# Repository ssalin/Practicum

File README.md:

# Practicum

adding the following libraries for eagle:

https://github.com/sparkfun/SparkFun-Eagle-Libraries
https://github.com/adafruit/Adafruit-Eagle-Library

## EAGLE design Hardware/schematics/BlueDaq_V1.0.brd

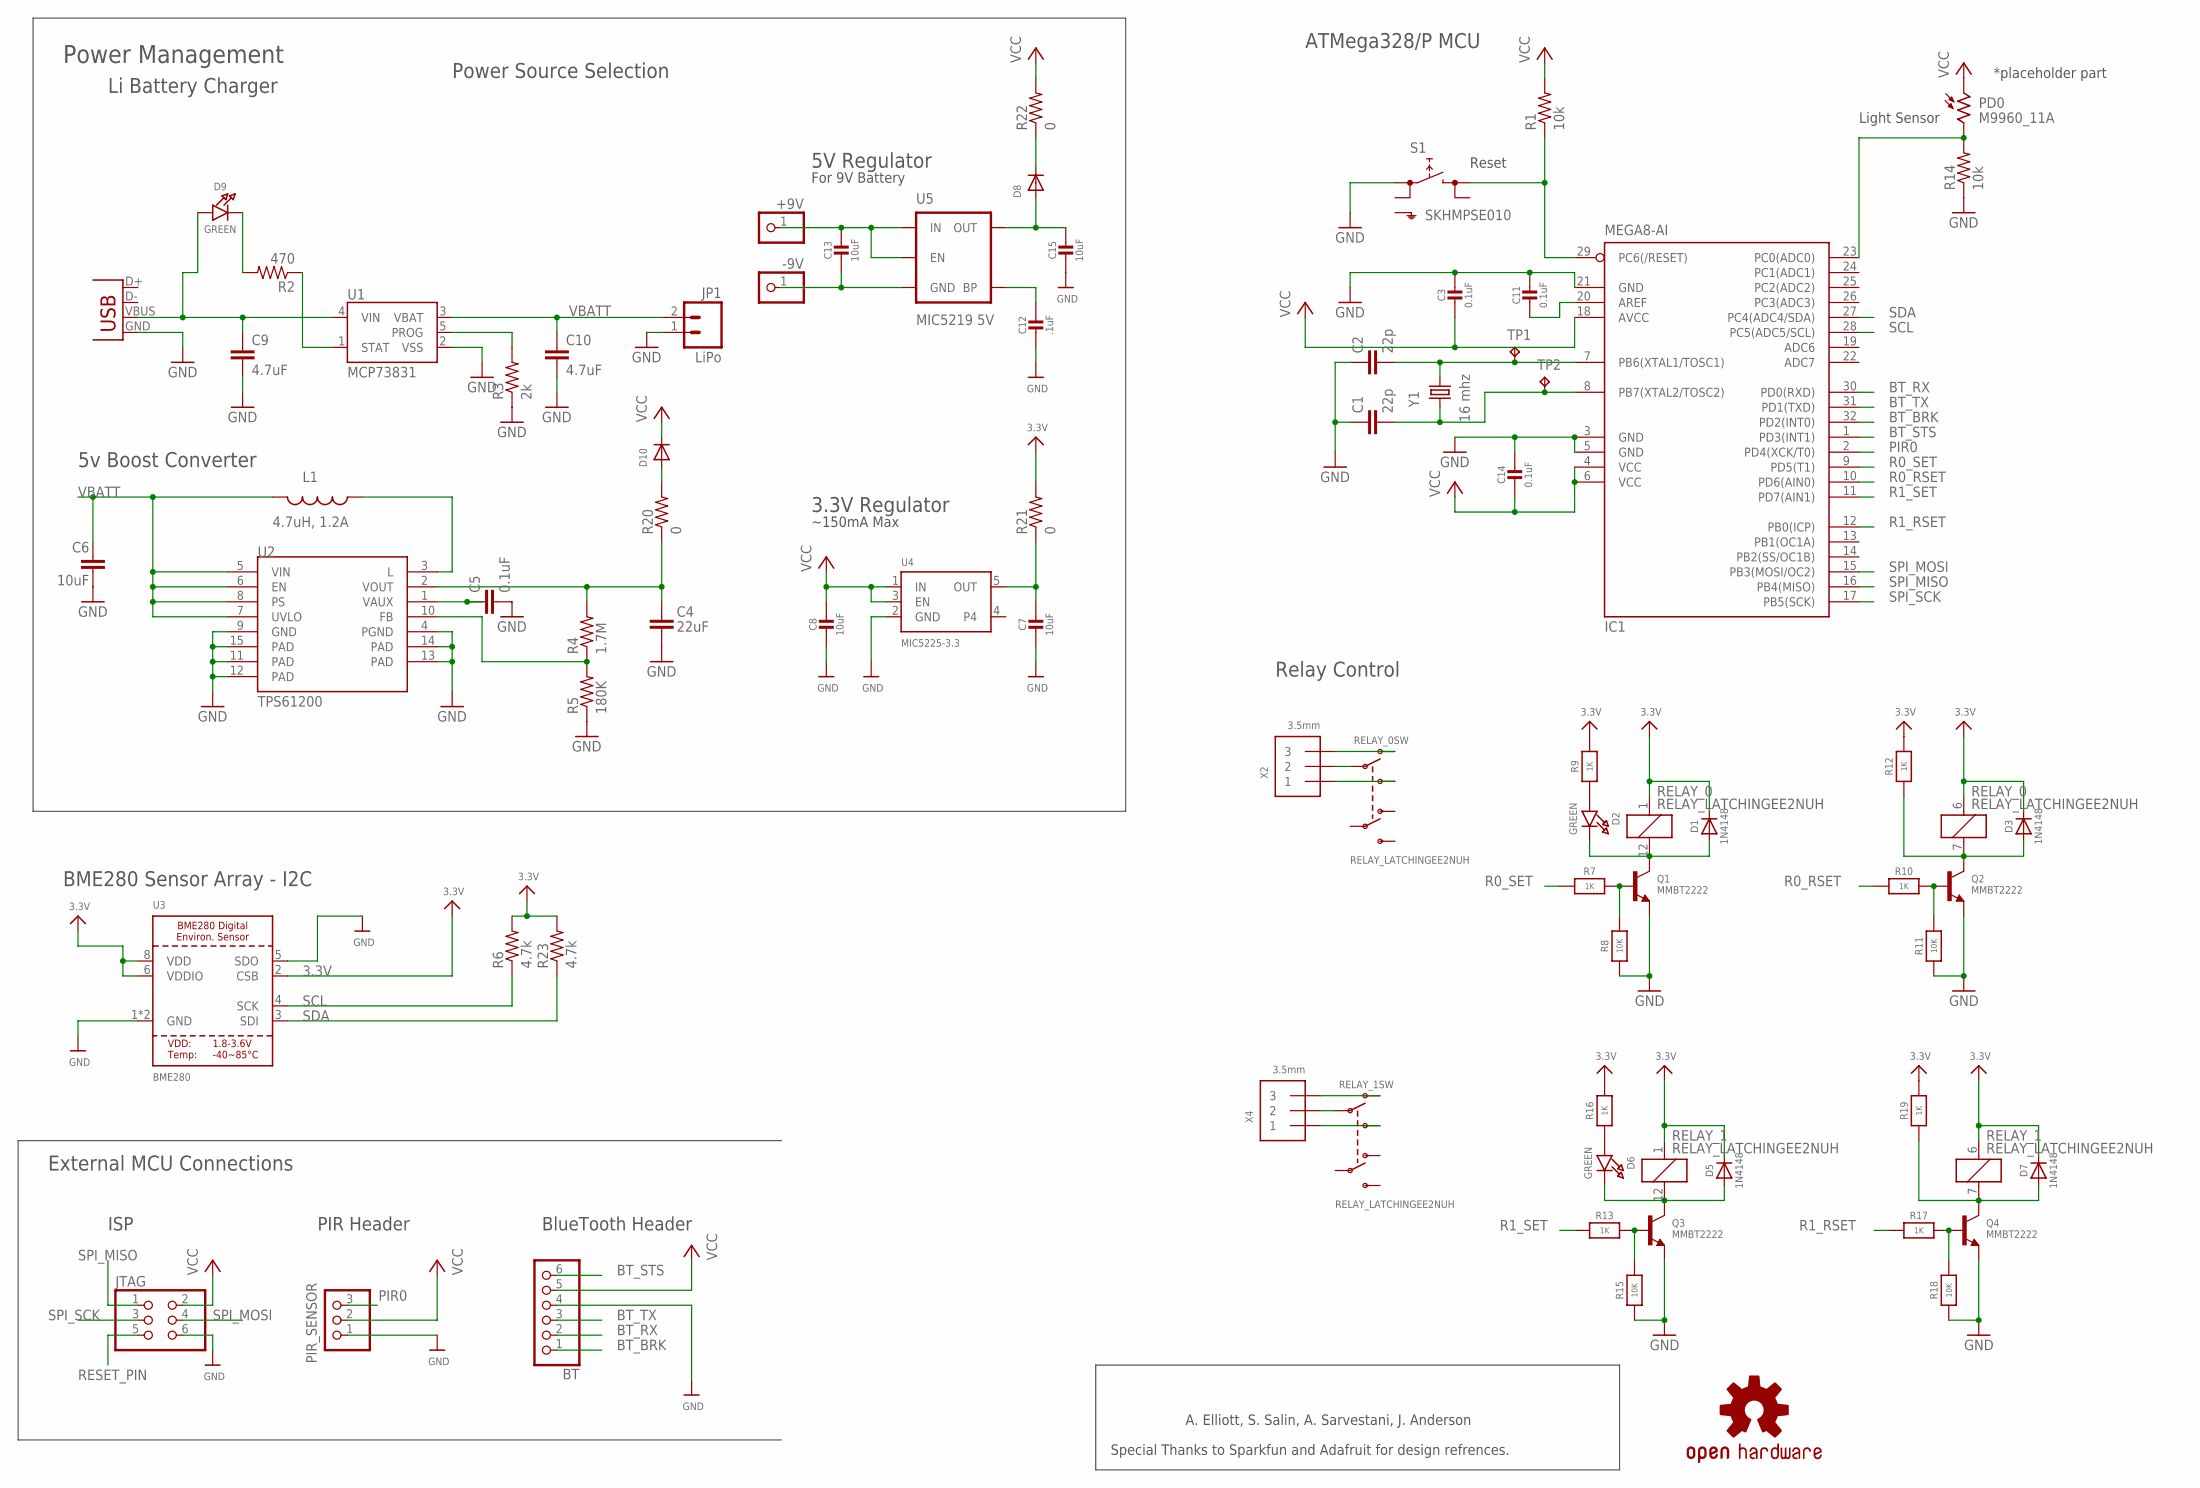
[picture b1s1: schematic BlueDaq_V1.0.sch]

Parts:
+9V: PINHD-1X1; 1X01
-9V: PINHD-1X1; 1X01
BT: PINHD-1X6; 1X06
C1, C2: 22p; C0805
C3, C11, C14: 0.1uF; 0805-NO@1
C4: 22uF; 0805
C5: 0.1uF; 0805
C6: 10uF; 1206
C7, C8, C13, C15: 10uF; 0805-NO@1
C9, C10: 4.7uF; 0805
C12: .1uF; 0805-NO@1
D1, D3, D5, D7: 1N4148; SOD-323
D2, D6, D9: GREEN; CHIPLED_0805_NOOUTLINE
D8, D10: DIODESMA; SMADIODE
IC1: MEGA8-AI; TQFP32-08
JP1: LiPo; JST-2-SMD
JTAG: PINHD-2X3; 2X03
L1: 4.7uH, 1.2A; CDRH2D09
PD0: M9960_11A; M9960
PIR_SENSOR: PINHD-1X3; 1X03
Q1, Q2, Q3, Q4: MMBT2222; SOT23-R
R1, R14: 10k; R0805
R2: 470; R0805
R3: 2k; R0805
R4: 1.7M; R0805
R5: 180K; R0805
R6, R23: 4.7k; R0805
R7, R9, R10, R12, R13, R16, R17, R19: 1K; 0805-NO
R8, R11, R15, R18: 10K; 0805-NO
R20, R21, R22: 0; R0805
RELAY_0, RELAY_1: RELAY_LATCHINGEE2NUH; RELAY_EE2_LATCH
S1: SKHMPSE010; SKHMPXE010
TP1, TP2: TPTP19SQ; TP19SQ
U1: MCP73831; SOT23-5
U2: TPS61200; QFN-10_PAD
U3: BME280
U4: MIC5225-3.3; SOT23-5
U5: MIC5219 5V; SOT23-5
U$22: OSHW-LOGOS; OSHW-LOGO-S
X1: USB-MICROB
X2, X4: 3.5mm; TERMBLOCK_1X3-3.5MM
Y1: 16 mhz; HC49U-V

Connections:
3.3V: D1.C, D3.C, D5.C, D7.C, R6.2, R9.2, R12.2, R16.2, R19.2, R21.2, R23.2, RELAY_0.1, RELAY_0.6 (1), RELAY_1.1, RELAY_1.6 (1), U3.2 (CSB), U3.6 (VDDIO), U3.8 (VDD)
BT_BRK: BT.1, IC1.32 (PD2(INT0))
BT_RX: BT.2, IC1.30 (PD0(RXD))
BT_STS: BT.6, IC1.1 (PD3(INT1))
BT_TX: BT.3, IC1.31 (PD1(TXD))
COM1: RELAY_0.9 (P1), X2.2
COM2: RELAY_1.9 (P1), X4.2
FB: R4.1, R5.2, U2.10 (FB)
GND: BT.4, C1.1, C2.1, C3.1, C4.2, C5.2, C6.2, C7.2, C8.2, C9.2, C10.2, C11.1, C12.2, C14.1, C15.2, IC1.3 (GND), IC1.5 (GND), IC1.21 (GND), JP1.1, JTAG.6, PIR_SENSOR.1, Q1.2 (E), Q2.2 (E), Q3.2 (E), Q4.2 (E), R3.1, R5.1, R8.1, R11.1, R14.1, R15.1, R18.1, S1.1 (1.1), U1.2 (VSS), U2.4 (PGND), U2.9 (GND), U2.11 (PAD), U2.12 (PAD), U2.13 (PAD), U2.14 (PAD), U2.15 (PAD), U3.1 (GND), U3.5 (SDO), U3.7 (GND), U4.2 (GND), X1.GND
unnamed: IC1.23 (PC0(ADC0)), PD0.2, R14.2
unnamed: L1.P$1 (1), U2.3 (L)
unnamed: C5.1, U2.1 (VAUX)
unnamed: D9.C, R2.2
unnamed: C15.1, D8.A, U5.5 (OUT)
unnamed: D1.A, D2.C, Q1.3 (C), RELAY_0.12 (2)
unnamed: D5.A, D6.C, Q3.3 (C), RELAY_1.12 (2)
unnamed: Q3.1 (B), R13.2, R15.2
unnamed: D6.A, R16.1
unnamed: RELAY_1.10 (O1), X4.3
unnamed: R3.2, U1.5 (PROG)
unnamed: D7.A, Q4.3 (C), R19.1, RELAY_1.7 (2)
unnamed: Q4.1 (B), R17.2, R18.2
unnamed: R2.1, U1.1 (STAT)
unnamed: +9V.1, C13.1, U5.1 (IN), U5.3 (EN)
unnamed: -9V.1, C13.2, U5.2 (GND)
unnamed: C12.1, U5.4 (BP)
unnamed: D8.C, R22.1
unnamed: D10.A, R20.2
unnamed: Q1.1 (B), R7.2, R8.2
unnamed: C9.1, D9.A, U1.4 (VIN), X1.VBUS
unnamed: D3.A, Q2.3 (C), R12.1, RELAY_0.7 (2)
unnamed: D2.A, R9.1
unnamed: Q2.1 (B), R10.2, R11.2
unnamed: RELAY_0.10 (O1), X2.3
unnamed: C11.2, IC1.20 (AREF)
NO1: RELAY_0.8 (S1), X2.1
NO2: RELAY_1.8 (S1), X4.1
OUT: C7.1, R21.1, U4.5 (OUT)
PIR0: IC1.2 (PD4(XCK/T0)), PIR_SENSOR.3
R0_RSET: IC1.10 (PD6(AIN0)), R10.1
R0_SET: IC1.9 (PD5(T1)), R7.1
R1_RSET: IC1.12 (PB0(ICP)), R17.1
R1_SET: IC1.11 (PD7(AIN1)), R13.1
RESET_PIN: IC1.29 (PC6(/RESET)), JTAG.5, R1.1, S1.3 (2.1)
SCL: IC1.28 (PC5(ADC5/SCL)), R6.1, U3.4 (SCK)
SDA: IC1.27 (PC4(ADC4/SDA)), R23.1, U3.3 (SDI)
SPI_MISO: IC1.16 (PB4(MISO)), JTAG.1
SPI_MOSI: IC1.15 (PB3(MOSI/OC2)), JTAG.4
SPI_SCK: IC1.17 (PB5(SCK)), JTAG.3
VBATT: C6.1, C10.1, JP1.2, L1.P$2 (2), U1.3 (VBAT), U2.5 (VIN), U2.6 (EN), U2.7 (UVLO), U2.8 (PS)
VCC: BT.5, C3.2, C8.1, C14.2, D10.C, IC1.4 (VCC), IC1.6 (VCC), IC1.18 (AVCC), JTAG.2, PD0.1, PIR_SENSOR.2, R1.2, R22.2, U4.1 (IN), U4.3 (EN)
VOUT: C4.1, R4.2, R20.1, U2.2 (VOUT)
XTAL1: C2.2, IC1.7 (PB6(XTAL1/TOSC1)), TP1.TP, Y1.2
XTAL2: C1.2, IC1.8 (PB7(XTAL2/TOSC2)), TP2.TP, Y1.1

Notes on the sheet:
Li Battery Charger
5v Boost Converter
ATMega328/P MCU
Reset
External MCU Connections
BME280 Sensor Array - I2C
~150mA Max
3.3V Regulator
ISP
PIR Header
BlueTooth Header
Light Sensor
*placeholder part
Relay Control
5V Regulator
For 9V Battery
Power Source Selection
Power Management
A. Elliott, S. Salin, A. Sarvestani, J. Anderson
Special Thanks to Sparkfun and Adafruit for design refrences.

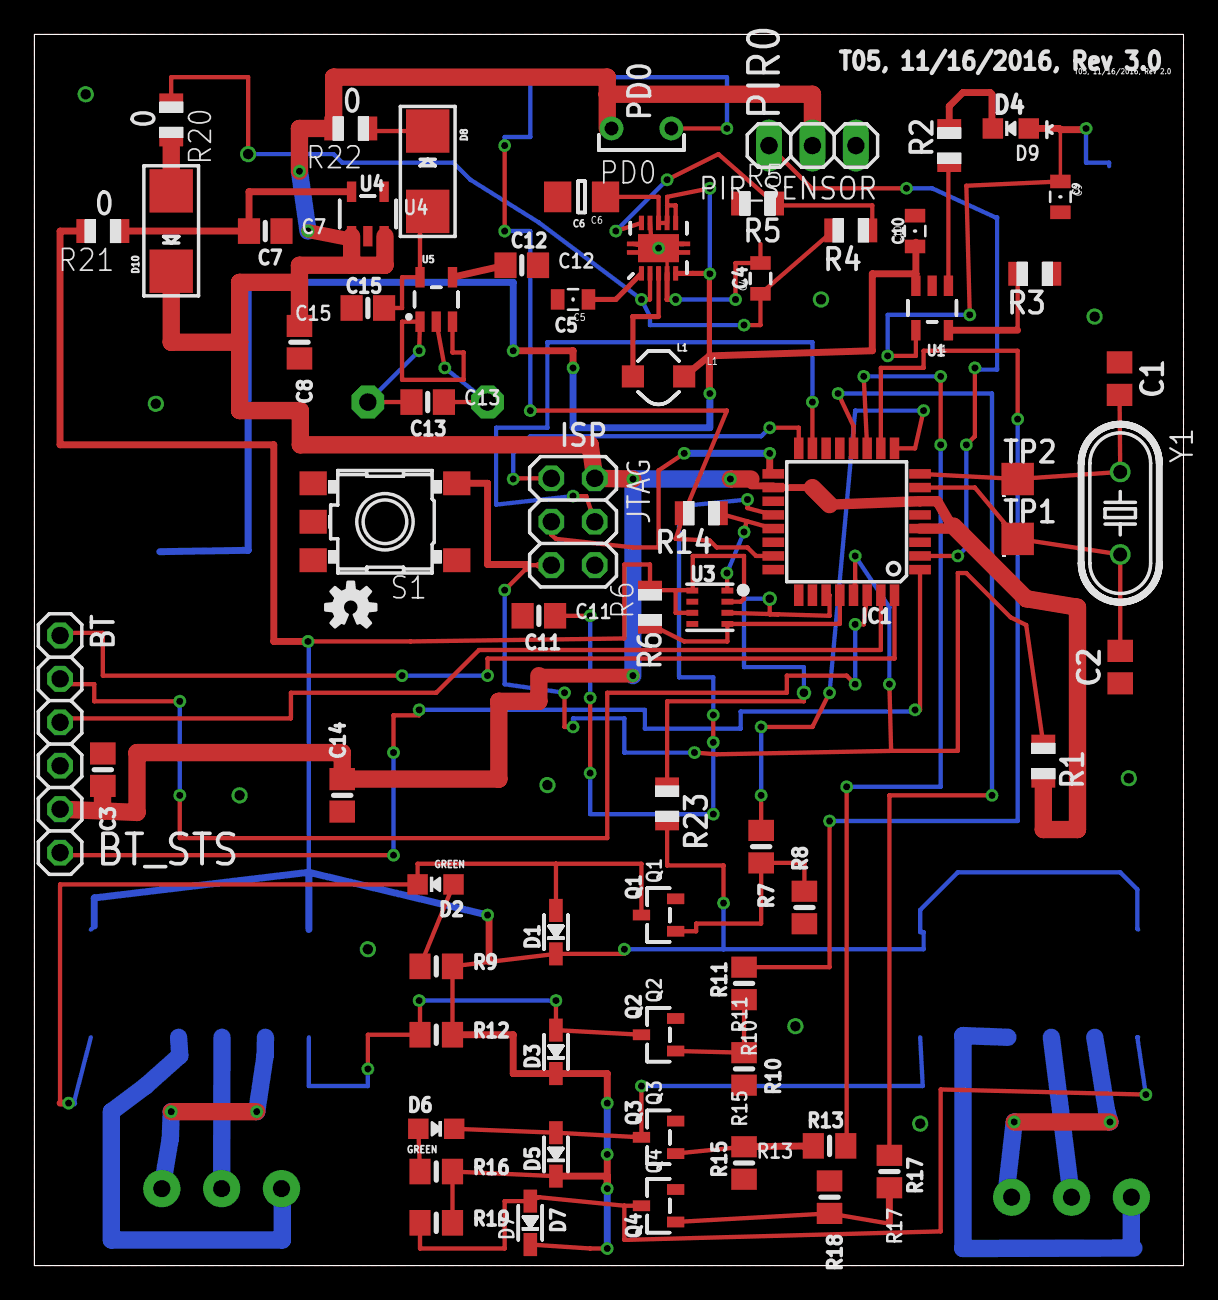
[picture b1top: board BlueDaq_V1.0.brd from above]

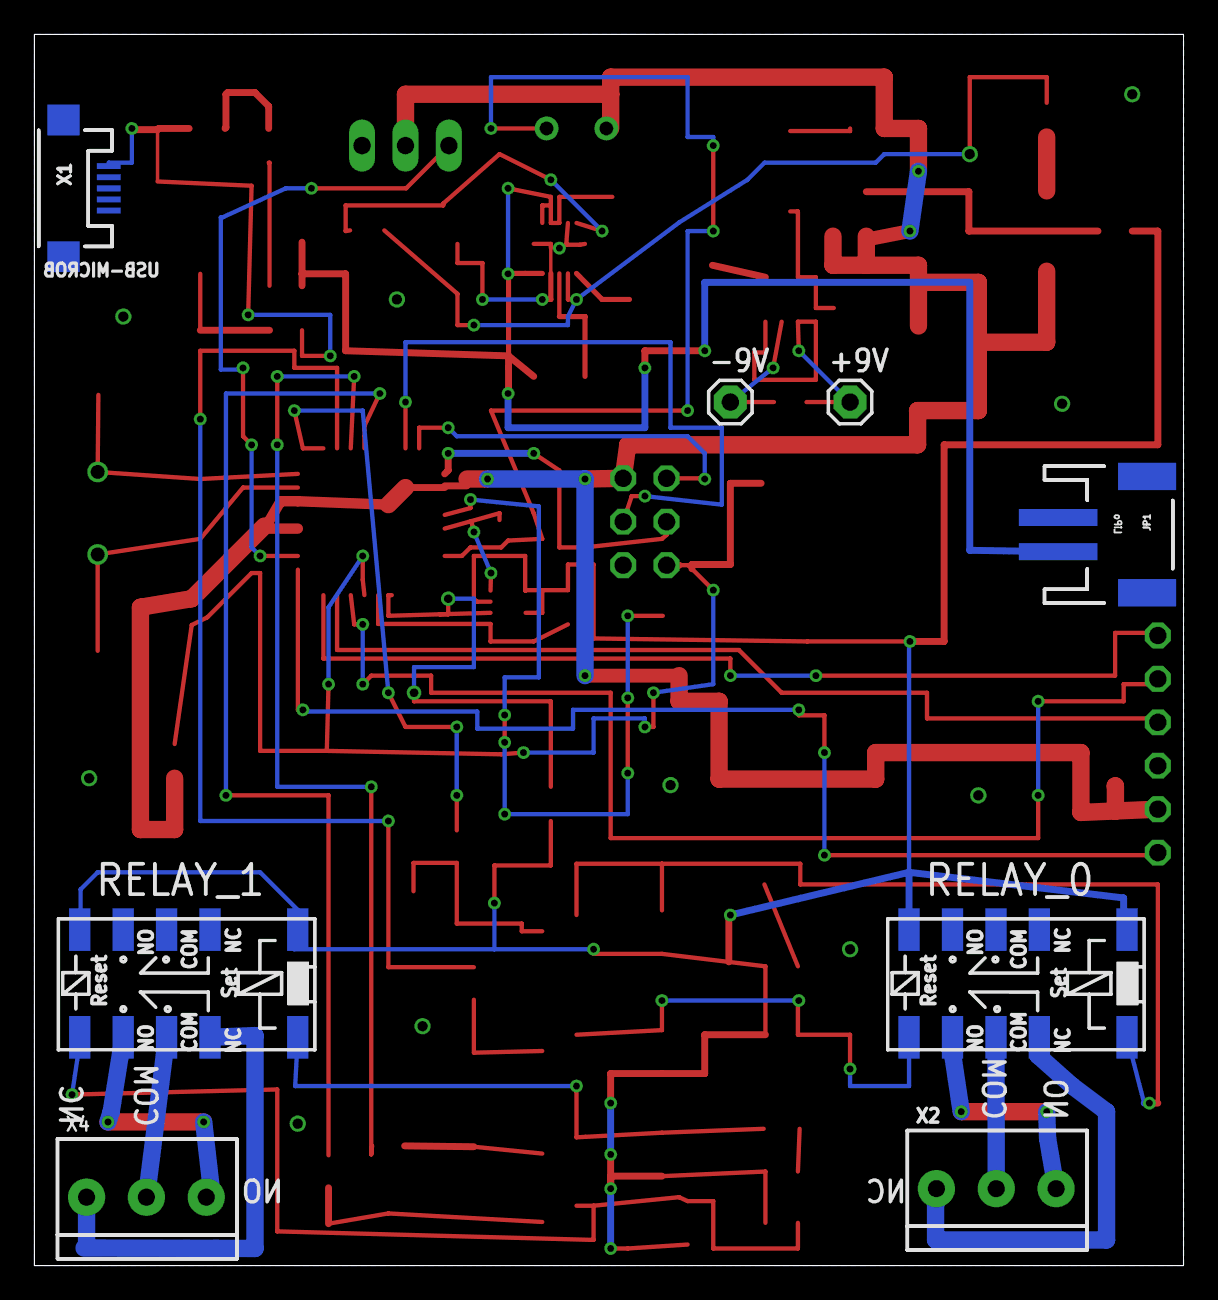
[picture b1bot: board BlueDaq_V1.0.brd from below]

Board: 2 copper layers, 67.2 x 72.0 mm, 75 parts (8 on the bottom side), 54 nets.

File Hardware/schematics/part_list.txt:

Partlist

Exported from BlueDaq_V1.0.brd at 11/17/2016 1:10 PM

EAGLE Version 7.6.0 Copyright (c) 1988-2016 CadSoft

Assembly variant: 

Part       Value                Package                Library           Position (mm)         Orientation

+9V                             1X01                   adafruit          (19.5 50.5)           MR0
-9V                             1X01                   adafruit          (26.5 50.5)           MR0
BT                              1X06                   adafruit          (1.5 30.5)            R270
C1         22p                  C0805                  rcl               (63.46 51.87)         R270
C2         22p                  C0805                  rcl               (63.5 35)             R90
C3         0.1uF                0805-NO@1              microbuilder      (4 29)                R270
C4         22uF                 0805                   CH_passive        (42.46 57.73)         R90
C5         0.1uF                0805                   SparkFun          (31.5 56.5)           R180
C6         10uF                 1206                   CH_passive        (32 62.5)             R180
C7         10uF                 0805-NO@1              microbuilder      (13.5 60.5)           R0
C8         10uF                 0805-NO@1              microbuilder      (15.5 54)             R270
C9         4.7uF                0805                   SparkFun          (60 62.5)             R270
C10        4.7uF                0805                   SparkFun          (51.5 60.5)           R90
C11        0.1uF                0805-NO@1              microbuilder      (29.5 38)             R0
C12        .1uF                 0805-NO@1              microbuilder      (28.5 58.5)           R0
C13        10uF                 0805-NO@1              microbuilder      (23 50.5)             R0
C14        0.1uF                0805-NO@1              microbuilder      (18 27.5)             R90
C15        10uF                 0805-NO@1              microbuilder      (19.5 56)             R180
D1         1N4148               SOD-323                microbuilder      (30.5 19.5)           R90
D2         GREEN                CHIPLED_0805_NOOUTLINE microbuilder      (23.46 22.29)         R90
D3         1N4148               SOD-323                microbuilder      (30.5 12.5)           R90
D5         1N4148               SOD-323                microbuilder      (30.5 6.5)            R90
D6         GREEN                CHIPLED_0805_NOOUTLINE microbuilder      (23.5 8)              R270
D7         1N4148               SOD-323                microbuilder      (29 2.5)              R90
D8                              SMADIODE               adafruit          (23 64)               R270
D9         GREEN                CHIPLED_0805_NOOUTLINE microbuilder      (57.1 66.5)           R90
D10                             SMADIODE               adafruit          (8 60.5)              R90
IC1        MEGA8-AI             TQFP32-08              atmel             (47.5 43.5)           R180
JP1        LiPo                 JST-2-SMD              SparkFun          (3.63 42.75)          MR270
JTAG                            2X03                   pinhead           (31.5 43.5)           R270
L1         4.7uH, 1.2A          CDRH2D09               SparkFun          (36.5 52)             R0
PD0        M9960_11A            M9960                  photo-elements    (35.5 66.5)           R0
PIR_SENSOR                      1X03                   pinhead           (45.5 65.5)           R180
Q1         MMBT2222             SOT23-R                microbuilder      (36.5 20.5)           R90
Q2         MMBT2222             SOT23-R                microbuilder      (36.5 13.5)           R90
Q3         MMBT2222             SOT23-R                microbuilder      (36.5 7.5)            R90
Q4         MMBT2222             SOT23-R                microbuilder      (36.5 3.5)            R90
R1         10k                  R0805                  adafruit          (59 29.5)             R270
R2         470                  R0805                  adafruit          (53.5 65.5)           R90
R3         2k                   R0805                  adafruit          (58.5 58)             R180
R4         1.7M                 R0805                  adafruit          (47.74 60.54)         R180
R5         180K                 R0805                  adafruit          (42.29 62.11)         R0
R6         4.7k                 R0805                  adafruit          (36 38.5)             R90
R7         1K                   0805-NO                microbuilder      (42.5 24.5)           R270
R8         10K                  0805-NO                microbuilder      (45.03 20.94)         R90
R9         1K                   0805-NO                microbuilder      (23.5 17.5)           R0
R10        1K                   0805-NO                microbuilder      (41.5 16.5)           R270
R11        10K                  0805-NO                microbuilder      (41.5 11.5)           R90
R12        1K                   0805-NO                microbuilder      (23.5 13.5)           R0
R13        1K                   0805-NO                microbuilder      (46.5 7)              R180
R14        10k                  R0805                  adafruit          (39 44)               R180
R15        10K                  0805-NO                microbuilder      (41.5 6)              R90
R16        1K                   0805-NO                microbuilder      (23.5 5.5)            R0
R17        1K                   0805-NO                microbuilder      (50 5.5)              R270
R18        10K                  0805-NO                microbuilder      (46.5 4)              R270
R19        1K                   0805-NO                microbuilder      (23.5 2.5)            R0
R20        0                    R0805                  adafruit          (8 67)                R270
R21        0                    R0805                  adafruit          (4 60.5)              R180
R22        0                    R0805                  adafruit          (18.5 66.5)           R180
R23        4.7k                 R0805                  adafruit          (37 27)               R270
RELAY_0    RELAY_LATCHINGEE2NUH RELAY_EE2_LATCH        microbuilder      (9.5 16.5)            MR180
RELAY_1    RELAY_LATCHINGEE2NUH RELAY_EE2_LATCH        microbuilder      (58 16.5)             MR180
S1         SKHMPSE010           SKHMPXE010             switch            (20.5 43.5)           R180
TP1        TPTP19SQ             TP19SQ                 testpad           (57.5 42.5)           R0
TP2        TPTP19SQ             TP19SQ                 testpad           (57.5 46)             R0
U1         MCP73831             SOT23-5                SparkFun          (52.5 56)             R180
U2         TPS61200             QFN-10_PAD             SparkFun          (36.5 59.5)           R0
U3         BME280               BME280                 microbuilder      (39.5 38.5)           R0
U4         MIC5225-3.3          SOT23-5                microbuilder      (19.5 61.5)           R0
U5         MIC5219 5V           SOT23-5                SparkFun-PowerIC  (23.5 56.5)           R0
X1         USB-MICROB           USB-MICROB             SparkFun          (65.5 63)             MR270
X2         3.5mm                TERMBLOCK_1X3-3.5MM    microbuilder      (11 4.5)              MR0
X4         3.5mm                TERMBLOCK_1X3-3.5MM    microbuilder      (60.7 4)              MR0
Y1         16 mhz               HC49U-V                SparkFun-FreqCtrl (63.5 44)             R270

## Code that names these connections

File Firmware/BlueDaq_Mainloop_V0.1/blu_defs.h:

/*
 * BluDaq Firmware
 * Macro Definitions File
 * Nov 2016
 * 
 */

//
//  Libraries and Refrences:
//






//
// Debug and Option Flags:
//

//#define DEBUG_EN   // Disable Auth
#define SERIAL_EN  // Enable Serial Debug Statements



//
// Defined Constants:
//

#define NUM_RELAY 2           // Number of Relays
//#define BAUD_RATE 115200      // Better Baud Rate for Serial
#define BAUD_RATE 9600        // Typical Baud Rate for Serial


//
// ATMega328/P Pin Definitions:
//

#define BT_STS 3        // BT Status Pin 
#define PIR0 4          // PIR motion sensor (active low)
#define R0_SET 5        // Set Relay 0
#define R0_RSET 6       // Reset Relay 0
#define R1_SET 7        // Set Relay 1
#define R1_RSET 8       // Reset Relay 1
#define LIGHT_SENSOR 0  // Analog 5v input



//
// Data Structures:
//

// Auth Data - For validating the host
typedef struct{
  bool auth_set;    // Authentication Paired
  int touch;        // Last-updated (date/time)
  double key;       // Auth-key
  double poll_freq; // Polling Frequency (power management)
} auth_data;

// Sensor Data - Stores "current" values
typedef struct{

  int ls;               // Light Sensor Analog Value (0-1023)
  bool PIR;             // Motion Sensor State
  float temp;           // Temperature
  float pressure;       // Pressure
  float humidity;       // Humidity
} sensor_data;

// Automation - Settings for Relay automation
typedef struct {

  // Relay 0 Automation Flags (1 byte):
  byte en   : 1;   // Enable
  byte dec  : 1;   // Descending set point
  byte tog  : 1;   // Toggle Relay
  byte tmp  : 1;   // Temperature Sensor
  byte pres : 1;   // Pressure Sensor
  byte hum  : 1;   // Humidity sensor
  byte ls   : 1;   // Light sensor
  byte pir  : 1;   // PIR Motion Sensor

  float setpoint_0;   // Setpoint 
  int t_duration_0;   // Toggle Duration
} auto_data;
 


//
// EEPROM Settings:
//

#define EEPROM_SIZE 1024;     // Size of EEPROM in Bytes
#define AUTH_ADDR 0            // Address of Authentication Structure
#define AUTO_ADDR 12            // Address of Automation Structure(s)
#define AUTO_SIZE 7            // Size of Automation Struct, 7 per struct, 14 for both structs
#define AUTH_SIZE 11            // Size of Authentication Struct

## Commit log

2016-10-09 Create gh-pages branch via GitHub
2016-10-13 Rename hardware/PCB/PCB_notes.txt to hardwares/schematics/schamatic_notes.txt
2016-10-13 Rename schamatic_notes.txt to schematic_notes.txt
2016-10-13 Rename hardwares/schematics/schematic_notes.txt to hardware/schematics/schematic_notes.txt
2016-10-18 - Organized Directories + Added all team planning documents
2016-10-20 + Firmware Template
2016-10-20 + Added several files to hardware dev
2016-10-20 + For Sam :)
2016-10-20 Added Simulation of SR_latch 1.1
2016-10-26 Battery Charger/Booster Schematic
2016-10-27 Changes 0.2
    Adjust input voltage with sqaure wave
2016-10-27 New Changes 0.3
2016-10-27 schematic additions
    added power schematics
2016-11-01 schem update
    updated the schematic some
2016-11-01 more updated schematic
2016-11-01 better headers
    fixed bluetooth header. still need to change PNP transistors to NMOS.
2016-11-02 NMOS, reorganized
    Switched NPN transistors for N-channel MOSFETs, Moved things around to
    make schem more readable
2016-11-03 + Lots of changes and corrections - Does not meet DRC Yet - Still need to implement option to swap out power supplies from 9V battery to LiOn
2016-11-03 + Design meets DRC
2016-11-03 Licensing information and Attributions
2016-11-04 Very preliminary start board layout
2016-11-05 T05 - Project Schedule
    This is a work in progress.
2016-11-05 updated layout
    preliminary bad layout done
2016-11-05 made grid smaller
2016-11-05 moved some stuff to other side of board
    starting to make big things on top small stuff on bottom for oven
2016-11-06 Some updates. Still working on it.
2016-11-07 + Firmware Flowchart
2016-11-07 Added Store and Load function.
2016-11-07 updated board
    updated layout. starting to have issue connecting gnd properly. added DRU/cam processor for OSH
2016-11-07 no more airwires, only need to clear DRC
    everything is router now, for better or worse
2016-11-07 removed errors
    less DRC errors
2016-11-07 removed DRC errors
2016-11-08 Added in Wire library
2016-11-08 + Pin and Structs added to defs
2016-11-08 T05 Project Schedule
2016-11-09 + Updated Firmware Diagram + Moved Project Planning Docs
2016-11-09 + Started WPF Windows Host App
2016-11-09 removed more DRC errors
2016-11-09 no more DRC errors!
2016-11-10 EEPROM
    Get and Put function implemented. Load and Store to EEPROM.
2016-11-10 Layout image for Wiki
2016-11-10 Project Schedule Image
2016-11-11 + Updated FW Diagram
2016-11-11 + Layout Proposal
2016-11-11 + Corrected Structs and housekeeping
2016-11-11 Struct Constructors
2016-11-13 prettier, no DRC errors
2016-11-13 Revert "Struct Constructors"
    This reverts commit d896c1534da5dee60c4173977d94653d818336d6.
2016-11-13 made vcc line beefier
2016-11-14 Constructors for EEPROM structs
2016-11-14 Polling Frequency Script
2016-11-15 + Updated Schematic
2016-11-15 + Firmware Updates
2016-11-15 Updated Struct size
2016-11-15 Timeone Library
2016-11-15 Create Alternate Layout
2016-11-15 Deleted this file (Created by accident)
2016-11-15 New layout
2016-11-16 + BT Test
2016-11-16 + Updated (other) schematic
2016-11-16 minor layout change
2016-11-16 more small layout changes
2016-11-16 fixed relay, made board smaller
2016-11-16 more small fixes
2016-11-16 Main Loop structure
    Migrated EEPROM and Polling with main loop
2016-11-16 cleaned up eagle
2016-11-16 Board update
2016-11-16 trace size fixes
2016-11-16 Some fat traces added
    Making it girthy
2016-11-16 More fat traces
2016-11-16 + Minor Changes to Schematic
2016-11-16 added new diode
2016-11-16 minor compression
2016-11-16 more compression
    whole board smaller
2016-11-16 more small fix
2016-11-16 GIRTH
    Maxed out Vcc girth
2016-11-16 took out the trash
    got rid of eagle garbage
2016-11-16 added silk layer
    silkscreen so fine so fresh so clean
2016-11-16 made edges straight
2016-11-16 added layout image
    1200 DPI SONNNN
2016-11-16 + orginization chages
2016-11-16 + organization updates
2016-11-16 andrew updates
2016-11-16 names
2016-11-16 cleaned up traces a little
2016-11-16 lots of changes
2016-11-16 placed new things, still need to do more routing
2016-11-17 more routed
2016-11-17 All traces are routed
2016-11-17 fixed silk
2016-11-17 removed DRC
2016-11-17 fixed gnd poly
2016-11-17 Minor fixes
2016-11-17 image
2016-11-17 naming
    special for andy
2016-11-17 Corrected posts to bottom layer
2016-11-17 + HW5
2016-11-17 udated image, part list
2016-11-17 oh no fix
2016-11-17 fixed comps being too dang small
2016-11-17 + small silk update
2016-11-18 Some Progress
2016-11-18 Initial Load to EEPROMs
2016-11-18 Removed
2016-11-18 Main Loop
2016-11-20 cleaned up /schem/docs, some parts list work
2016-11-20 Updated Firmware with Watchdog
2016-11-20 + BT Firmware Tests + iOS App: + Serial Connections work + Device can be selected / TX & RX + BlueDaq Communications defined (parser created) + Passcode function in debugging phase
2016-11-20 updated schematic
2016-11-20 + Complete Serial Message Stack
2016-11-20 + Restored parts list
2016-11-21 Updated .h file
2016-11-21 + Authentication between app and system now works + Serial Com Classes for Device and iOS improved
2016-11-21 better part list
2016-11-21 better-er parts list
    still need to add prices for everything
2016-11-21 Added prices
2016-11-22 + Firmware Updates + iOS App - In process of adding additional views. + Now saves prefs
2016-11-22 Added more pricing
2016-11-22 updated cost math a bit
2016-11-22 + Fixed Date Logging + Added Info Screen + Forward VC Data now working
2016-11-22 + Updates
2016-11-23 + Fixed Persistence Issue between views (segue data methods with storage class) + GUI for sensors and automation added
2016-11-23 Jelon's Working Folder
2016-11-23 RX functions
2016-11-24 Revert "RX functions"
    This reverts commit 5e96978ff3bc8db5ebb591c321004092b8fbfd2d.
2016-11-24 Back
2016-11-24 Test Plan
2016-11-24 Working Progress
2016-11-25 + Automation UI Work
2016-11-26 Progress
2016-11-27 Checkpoint
2016-11-28 Checkpoints
2016-11-28 solder stencil output
    hopefully it works
2016-11-29 + UI Changes
2016-11-29 + Automation View Completed
2016-11-29 More Changes/Updates
2016-11-29 + Sensor RX Functions Completed
2016-11-30 + gitignore
2016-11-30 Working Watchdog with EEPROM load and store
2016-11-30 Automation Template
2016-11-30 + Major Additions to Firmware
2016-12-01 Watchdog and EEPROM
2016-12-02 + Minor Changes to Sensor View
2016-12-02 Check in So i can work on my Laptop
2016-12-02 Changes for Parser
2016-12-04 Changes to RX Functions
2016-12-04 + Finished RX and TX sections of firmware (note some modifications to .h file)
2016-12-04 + Added toggle to Firmware RX + App sensor data working with parsing errors.
2016-12-04 EEPROM/Timer Checkpoint
2016-12-05 + Sensor View is working! - Automation is sending - but not recognized… + Manual automation settings are working (in debug mode)
2016-12-05 Added EEPROM and Watchdog
2016-12-05 EEPROM and Toggle Timer
2016-12-08 Revert Changes
2016-12-08 + Fixed some of the automation problems + Added several missing RX functions + Fixed bad RX functions
2016-12-08 Bill of materials pdf and excel
2016-12-08 + Updated App
2016-12-09 Updated Presentation
2016-12-09 +firmware changes

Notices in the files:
parts and their libraries:
SparkFun-FreqCtrl: Licensing: Creative Commons ShareAlike 4.0 International - https://creativecommons.org/licenses/by-sa/4.0
